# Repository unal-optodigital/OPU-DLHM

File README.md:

# Optical Pickup Units for DLHM: OPU-DLHM

This repo contains all the suplementary info and files related to the published paper "Adapting a Blu-ray Optical Pickup Unit as a Digital Lensless Holographic Microscopy Point Source". The circuit schematics and boards and the bill of materials will be found on this repo. As well as the most of our developements the info contained in this repo can be used for teaching and research purposes.

## Folders descriptions: 

- The circuit info folder contains the schematic and board design used to electronic-control of the OPU PHR-803T, the designs where adapted and modified from the schematics [presented by the team of Prof. Hwu](https://doi.org/10.1021/acssensors.8b00340).
- The bill of materials folder contains all the needed materials and some usefull .step CAD designs to incorporate the OPU in an standard 30 mm cage system. 

## Reference
Further information about this work can be found in the following publications. These are also the preferred way of citing this tool if you are implementing it in your own works.

- Heberley Tobón-Maya, Alejandra Gómez-Ramírez, Carlos Buitrago-Duque, and Jorge Garcia-Sucerquia, "Adapting a Blu-ray optical pickup unit as a point source for digital lensless holographic microscopy," Appl. Opt. 62, D39-D47 (2023).  
DOI: [10.1364/AO.474916](https://doi.org/10.1364/AO.474916).
- J. García-Sucerquia, C. Trujillo and J. F. Restrepo, "MICROSCOPIO, HOLOGRÁFICO SIN LENTES (MHDSL) Y MÉTODO PARA VISUALIZAR MUESTRAS," U.S. patent 7620179 (2018).

## Contact
- Jorge Garcia-Sucerquia ([jigarcia@unal.edu.co](mailto:jigarcia@unal.edu.co))
- Heberley Tobon-Maya (htobonm@unal.edu.co)
- Alejandra Gomez-Ramirez (alegomezram@unal.edu.co)
- Carlos A. Buitrago-Duque ([cabuitragod@unal.edu.co](mailto:cabuitragod@unal.edu.co))

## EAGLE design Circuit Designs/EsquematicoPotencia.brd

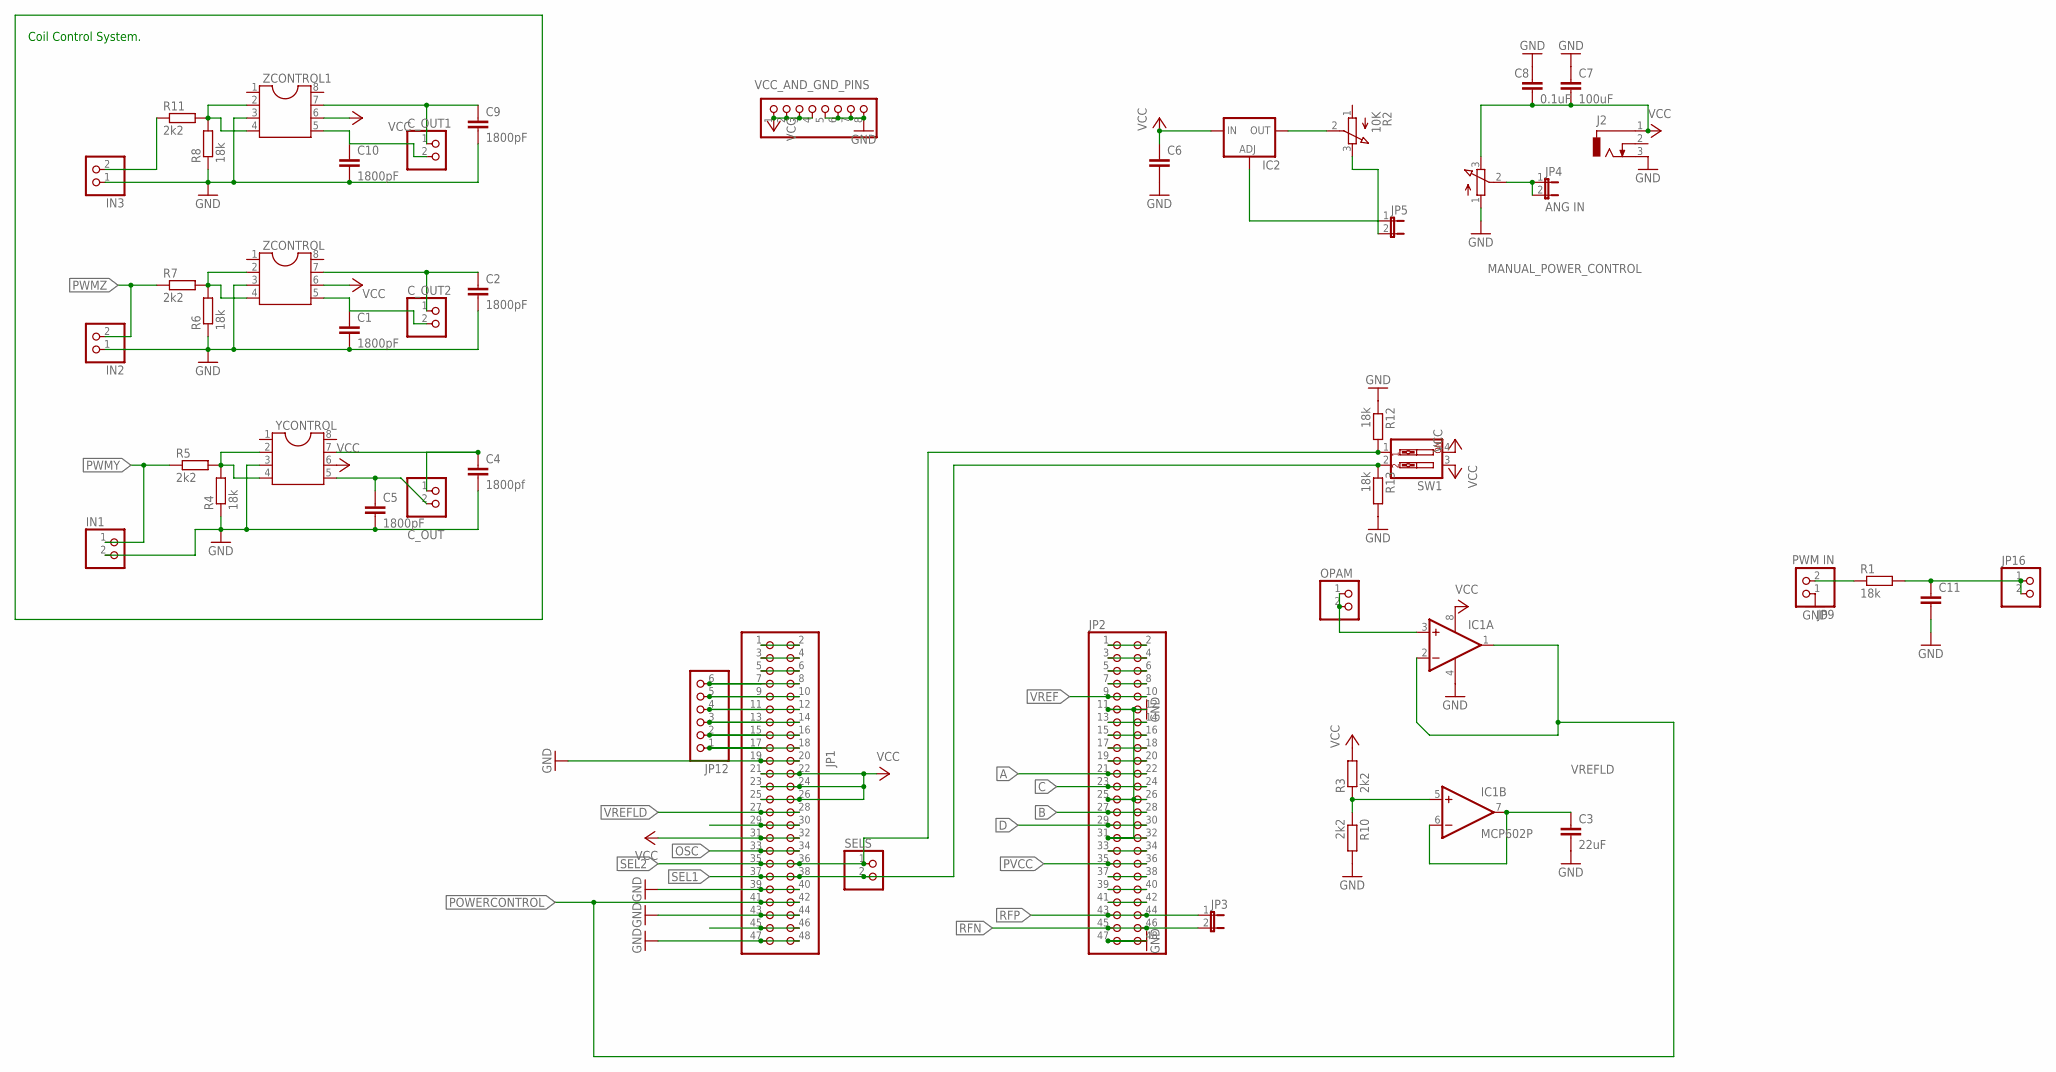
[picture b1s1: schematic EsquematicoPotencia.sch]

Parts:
C1, C2, C5, C9, C10: 1800pF; C025-024X044
C3: 22uF; C025-024X044
C4: 1800pf; C025-024X044
C6, C11: C-EU025-024X044; C025-024X044
C7: 100uF; C025-024X044
C8: 0.1uF; C025-024X044
C_OUT, C_OUT1, C_OUT2: PINHD-1X2; 1X02
IC1: MCP602P; DIL08
IC2: LM317TS; 317TS
IN1, IN2, IN3: PINHD-1X2; 1X02
J2: DCJ0303
JP1, JP2: PINHD-2X24; 2X24
JP3, JP5: JP1E; JP1
JP4: ANG IN; JP1
JP9: PWM IN; 1X02
JP12: PINHD-1X6; 1X06
JP16: PINHD-1X2; 1X02
MANUAL_POWER_CONTROL: 3RP/1610N
OPAM: PINHD-1X2; 1X02
R1, R4, R6, R8, R12, R13: 18k; 0204/7
R2: 10K; 3RP/1610N
R3, R5, R7, R10, R11: 2k2; 0204/7
SELS: PINHD-1X2; 1X02
SW1: SW_DIP-2; EDG-02
VCC_AND_GND_PINS: PINHD-1X8; 1X08
YCONTROL: DIL8; DIL08
ZCONTROL, ZCONTROL1: DIL8; DIL08

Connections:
A: JP2.21, JP2.22
B: JP2.27, JP2.28
C: JP2.23, JP2.24
D: JP2.29, JP2.30
GND: C1.2, C2.2, C3.2, C4.2, C5.2, C6.2, C7.1, C8.1, C9.2, C10.2, C11.2, IC1.4 (V-), IN1.2, IN2.1, IN3.1, J2.3, JP1.19, JP1.20, JP1.39, JP1.40, JP1.43, JP1.44, JP1.47, JP1.48, JP2.11, JP2.12, JP2.25, JP2.26, JP2.31, JP2.32, JP2.47, JP2.48, JP9.1, MANUAL_POWER_CONTROL.1 (A), R4.1, R6.1, R8.1, R10.2, R12.1, R13.2, VCC_AND_GND_PINS.5, VCC_AND_GND_PINS.6, VCC_AND_GND_PINS.7, VCC_AND_GND_PINS.8, YCONTROL.3, ZCONTROL.3, ZCONTROL1.3
unnamed: R8.2, R11.2, ZCONTROL1.2, ZCONTROL1.4
unnamed: JP1.1, JP1.2
unnamed: C11.1, JP16.1, JP16.2, R1.2
unnamed: R4.2, R5.2, YCONTROL.2, YCONTROL.4
unnamed: R6.2, R7.2, ZCONTROL.2, ZCONTROL.4
unnamed: JP1.29, JP1.30
unnamed: JP1.3, JP1.4
unnamed: IC1.5 (+IN), R3.1, R10.1
unnamed: JP4.1, JP4.2, MANUAL_POWER_CONTROL.2 (S)
unnamed: JP1.5, JP1.6
unnamed: JP2.1, JP2.2
unnamed: JP2.3, JP2.4
unnamed: JP1.45, JP1.46
unnamed: JP2.5, JP2.6
unnamed: JP2.7, JP2.8
unnamed: JP2.13, JP2.14
unnamed: JP2.15, JP2.16
unnamed: JP2.17, JP2.18
unnamed: JP2.19, JP2.20
unnamed: JP2.33, JP2.34
unnamed: JP2.37, JP2.38
unnamed: JP2.39, JP2.40
unnamed: JP2.41, JP2.42
unnamed: C2.1, C_OUT2.1, ZCONTROL.7
unnamed: C4.1, C_OUT.1, YCONTROL.7
unnamed: JP1.7, JP1.8, JP12.6
unnamed: C5.1, C_OUT.2, YCONTROL.5
unnamed: C1.1, C_OUT2.2, ZCONTROL.5
unnamed: JP9.2, R1.1
unnamed: IC1.3 (+IN), OPAM.1, OPAM.2
unnamed: IC2.1 (ADJ), JP5.1, JP5.2, R2.3 (E)
unnamed: IC2.2 (OUT), R2.2 (S)
unnamed: C9.1, C_OUT1.1, ZCONTROL1.7
unnamed: C10.1, C_OUT1.2, ZCONTROL1.5
unnamed: IN3.2, R11.1
OSC: JP1.33, JP1.34
POWERCONTROL: IC1.1 (OUT), IC1.2 (-IN), JP1.41, JP1.42
PVCC: JP2.35, JP2.36
PWMY: IN1.1, R5.1
PWMZ: IN2.2, R7.1
RFN: JP2.45, JP2.46, JP3.2
RFP: JP2.43, JP2.44, JP3.1
SEL1: JP1.37, JP1.38, R13.1, SELS.2, SW1.2
SEL2: JP1.35, JP1.36, R12.2, SELS.1, SW1.1
TILT2: JP1.17, JP1.18, JP12.1
VCC: C6.1, C7.2, C8.2, IC1.8 (V+), IC2.3 (IN), J2.1, JP1.21, JP1.22, JP1.23, JP1.24, JP1.25, JP1.26, JP1.31, JP1.32, MANUAL_POWER_CONTROL.3 (E), R3.2, SW1.3, SW1.4, VCC_AND_GND_PINS.1, VCC_AND_GND_PINS.2, VCC_AND_GND_PINS.3, VCC_AND_GND_PINS.4, YCONTROL.6, ZCONTROL.6, ZCONTROL1.6
VREF: JP2.9, JP2.10
VREFLD: C3.1, IC1.6 (-IN), IC1.7 (OUT), JP1.27, JP1.28
Y1: JP1.9, JP1.10, JP12.5
Y2: JP1.15, JP1.16, JP12.2
Z1: JP1.11, JP1.12, JP12.4
Z2: JP1.13, JP1.14, JP12.3

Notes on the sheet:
Coil Control System.

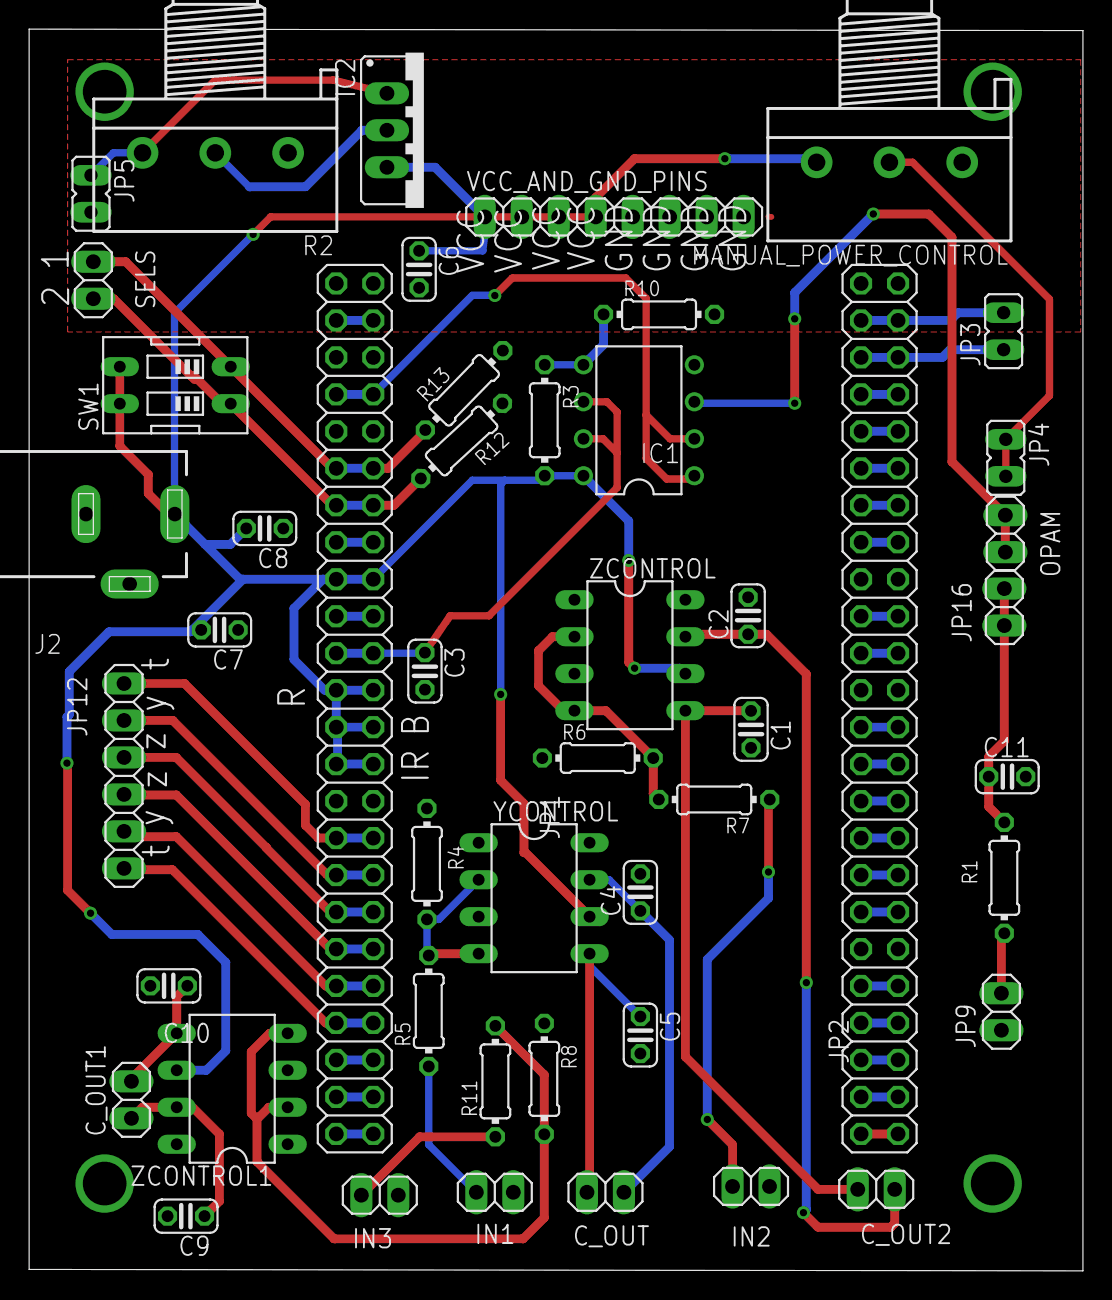
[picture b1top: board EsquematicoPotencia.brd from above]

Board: 2 copper layers, 72.4 x 85.3 mm, 48 parts (0 on the bottom side), 57 nets.

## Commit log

2022-07-08 Initial commit
    Initial commit with folders structure
2022-09-01 Update Materials.xlsx
    The BoM file has been updated
